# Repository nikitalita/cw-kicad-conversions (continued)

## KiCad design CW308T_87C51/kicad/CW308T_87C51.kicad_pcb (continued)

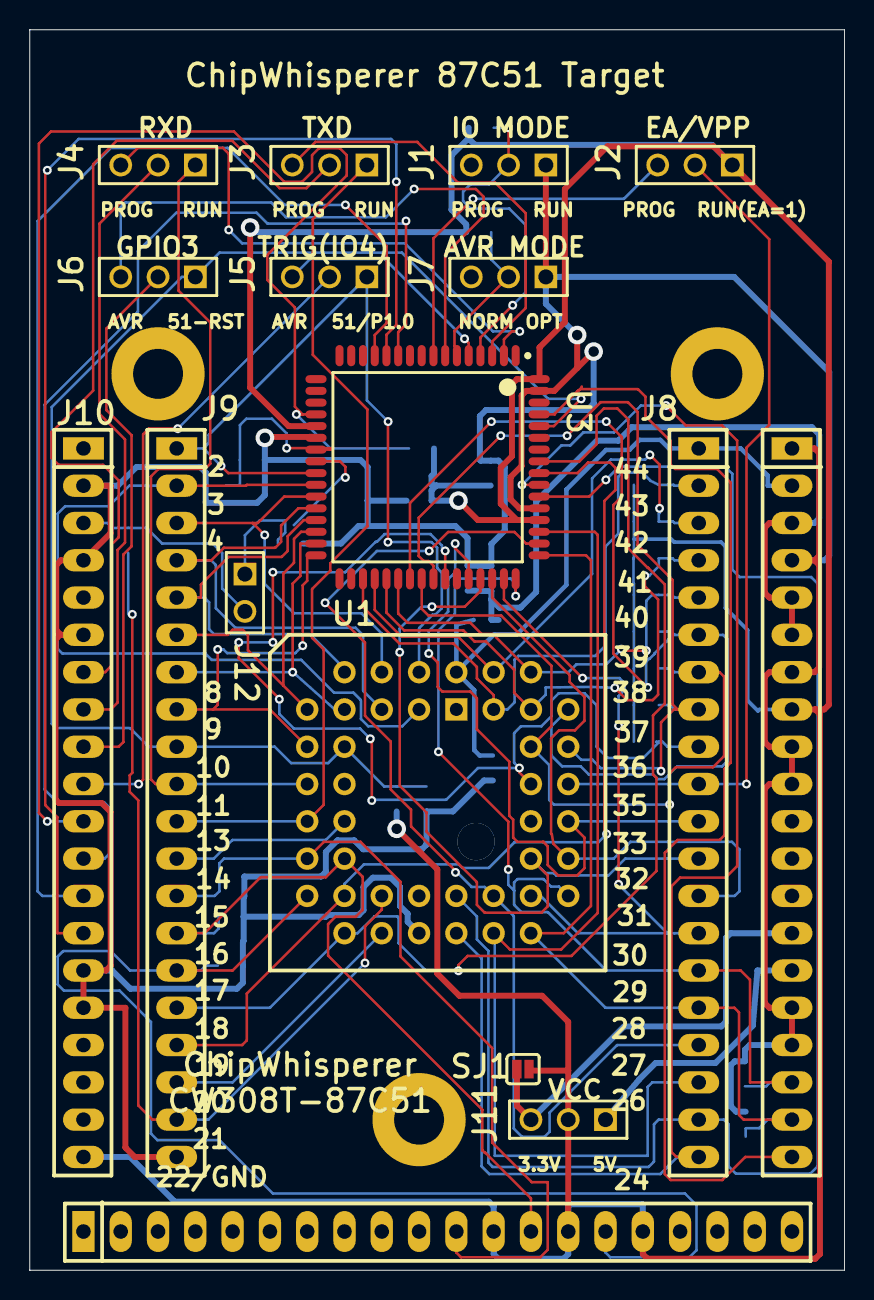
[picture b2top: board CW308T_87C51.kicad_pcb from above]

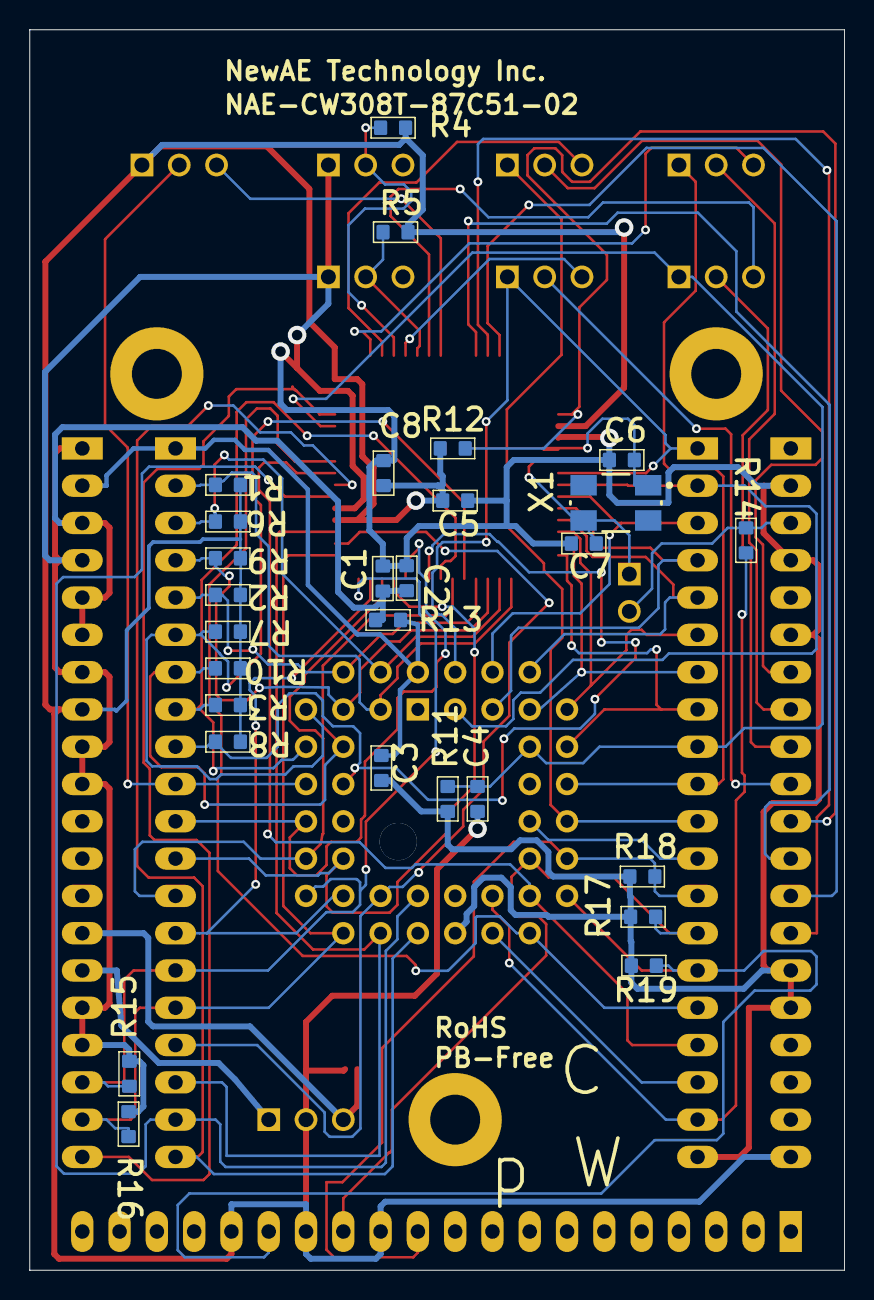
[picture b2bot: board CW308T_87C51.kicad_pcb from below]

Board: 2 copper layers, 55.5 x 84.5 mm, 43 parts (28 on the bottom side), 59 nets.

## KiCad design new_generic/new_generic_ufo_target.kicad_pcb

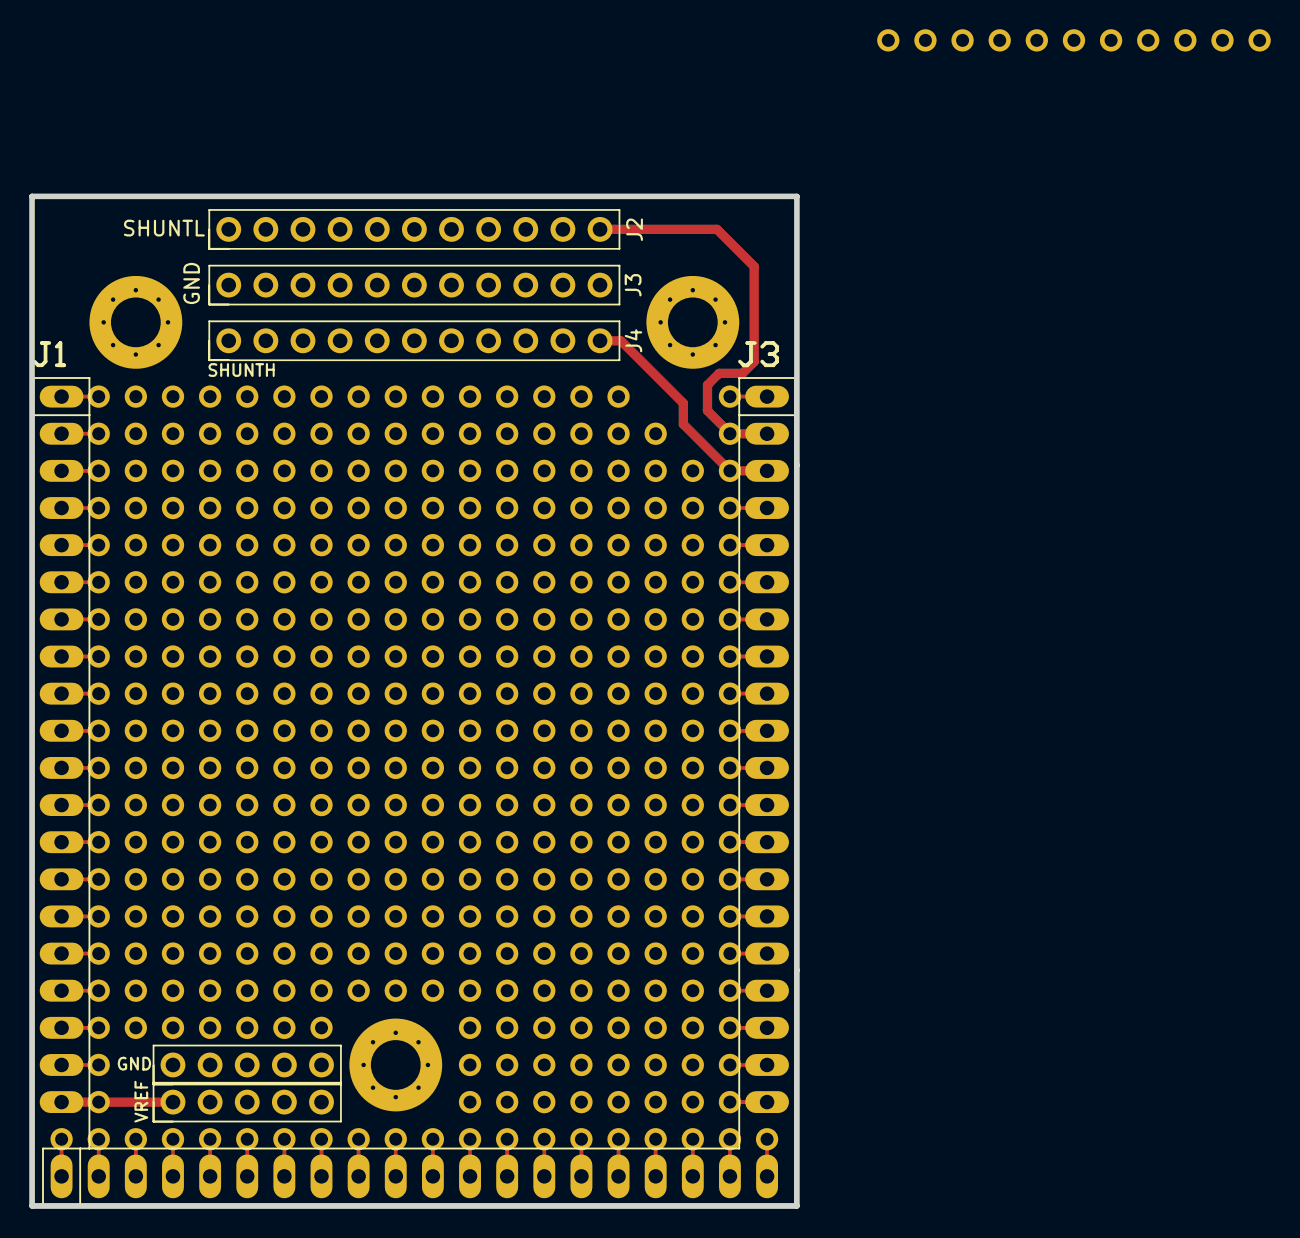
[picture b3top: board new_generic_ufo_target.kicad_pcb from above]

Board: 2 copper layers, 52.3 x 69.1 mm, 6 parts (0 on the bottom side), 4 nets.

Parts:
J1: CW308T_CONNBOARD
J2: SHUNTL; CONNECTED_PinHeader_1x11_P2.54mm_Vertical
J3: GND; CONNECTED_PinHeader_1x11_P2.54mm_Vertical
J4: SHUNTH; CONNECTED_PinHeader_1x11_P2.54mm_Vertical
J5: VREF; CONNECTED_PinHeader_1x05_P2.54mm_Vertical
J6: GND; CONNECTED_PinHeader_1x05_P2.54mm_Vertical

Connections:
GND: J1.A2 (GND), J1.A4 (GND), J1.A6 (GND), J1.A15 (GND), J1.A16 (GND), J1.C1 (GND), J1.C4 (GND), J1.C7 (GND), J1.C9 (GND), J1.C10 (GND), J1.C16 (GND), J1.C17 (GND), J3.1, J6.1
SHUNTH: J1.C3 (SHUNTH), J4.1
VBUS: J1.C2 (SHUNTL), J2.1
VCC: J1.A20 (VREF), J5.1

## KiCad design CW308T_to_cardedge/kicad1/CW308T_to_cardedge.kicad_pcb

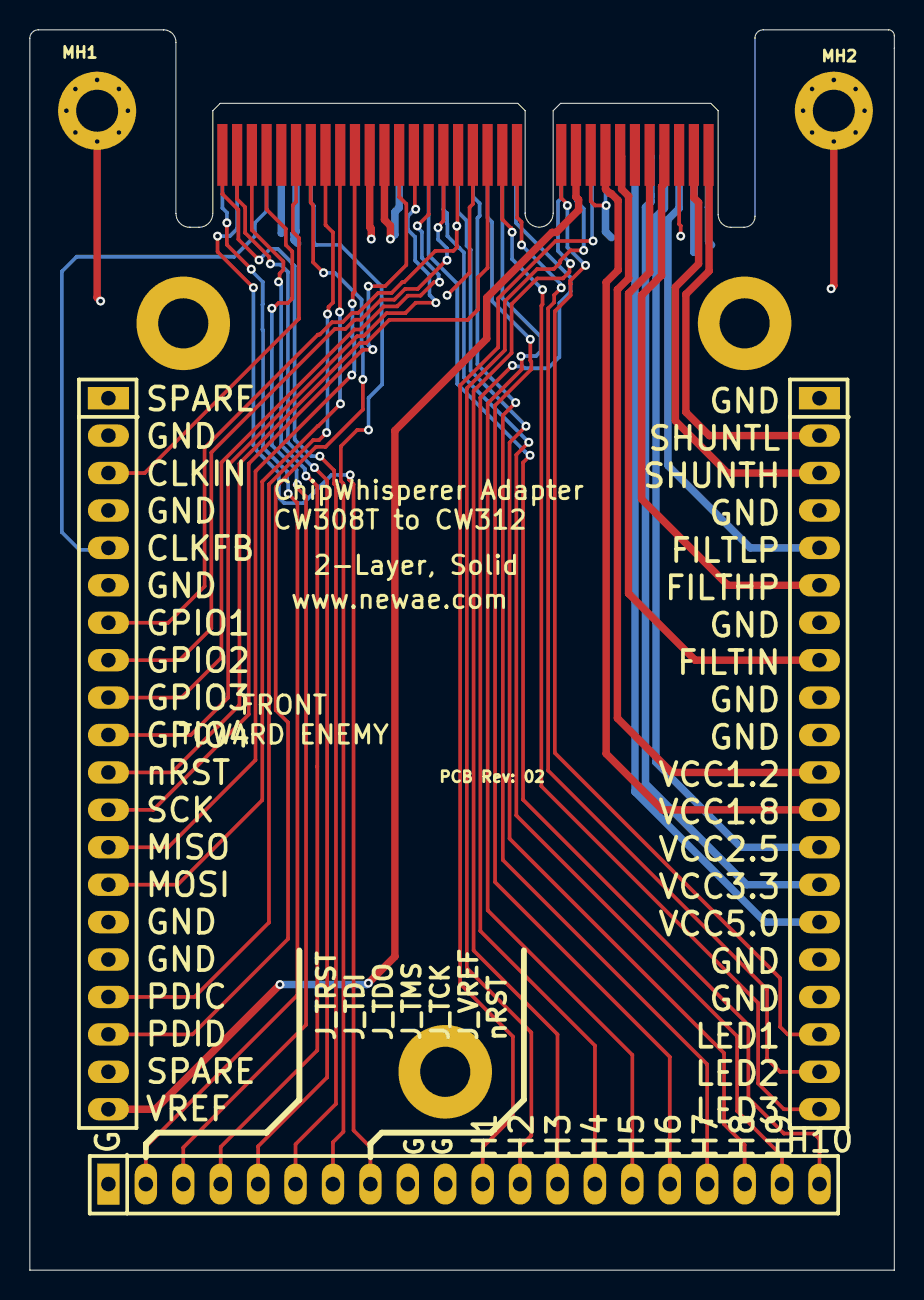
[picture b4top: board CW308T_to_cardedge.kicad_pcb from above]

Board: 2 copper layers, 58.7 x 84.2 mm, 4 parts (0 on the bottom side), 44 nets.

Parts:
J1: CW308_TARGETCON; _Users_cofly_Dropbox (NewAE Technology Inc)_engineering_alt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
MH1, MH2: 4-40 MH, Tight Fit; _Users_colin_Dropbox (NewAE Technology Inc)_engineering_alt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
P1: PCIeX4-GF-2D-1000-1K-O64

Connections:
CLKIN: J1.A5, P1.A29
CLKOUT: J1.A3, P1.B27
FILTIN: J1.C8, P1.B5
FILT_HP: J1.C6, P1.B4
FILT_LP: J1.C5, P1.A3
GND: J1.A2, J1.A4, J1.A6, J1.A15, J1.A16, J1.B1, J1.B9, J1.B10, J1.C1, J1.C4, J1.C7, J1.C9, J1.C10, J1.C16, J1.C17, MH1.1, MH2.1, P1.A1, P1.A2, P1.A8, P1.A20, P1.A27, P1.A28, P1.B3, P1.B9, P1.B15, P1.B21, P1.B22
GPIO1/TX: J1.A7, P1.B16
GPIO2/RX: J1.A8, P1.B17
GPIO3: J1.A9, P1.B18
GPIO4/TRIG: J1.A10, P1.B19
HDR1: J1.B11, P1.A9
HDR2: J1.B12, P1.A10
HDR3: J1.B13, P1.A11
HDR4: J1.B14, P1.A12
HDR5: J1.B15, P1.A13
HDR6: J1.B16, P1.A14
HDR7: J1.B17, P1.A15
HDR8: J1.B18, P1.A16
HDR9: J1.B19, P1.A17
HDR10: J1.B20, P1.A18
IOVREF: J1.A20, P1.B10
JTAG_TCK: J1.B6, P1.B32
JTAG_TDI: J1.B3, P1.B29
JTAG_TDO: J1.B4, P1.B30
JTAG_TMS: J1.B5, P1.B31
JTAG_TRST: J1.B2, P1.A32
JTAG_VREF: J1.B7, P1.A26
JTAG_nRST: J1.B8, P1.A31
LED1: J1.C18, P1.B11
LED2: J1.C19, P1.B12
LED3: J1.C20, P1.B13
MISO: J1.A13, P1.B23
MOSI: J1.A14, P1.B24
PDIC: J1.A17, P1.B25
PDID: J1.A18, P1.B26
SCK: J1.A12, P1.B20
SHUNTH: J1.C3, P1.B2
SHUNTL: J1.C2, P1.B1
VCC1.2: J1.C11, P1.B7
VCC1.8: J1.C12, P1.B8
VCC2.5: J1.C13, P1.A4
VCC3.3: J1.C14, P1.A5
VCC5.0: J1.C15, P1.A6
nRST: J1.A11, P1.B14

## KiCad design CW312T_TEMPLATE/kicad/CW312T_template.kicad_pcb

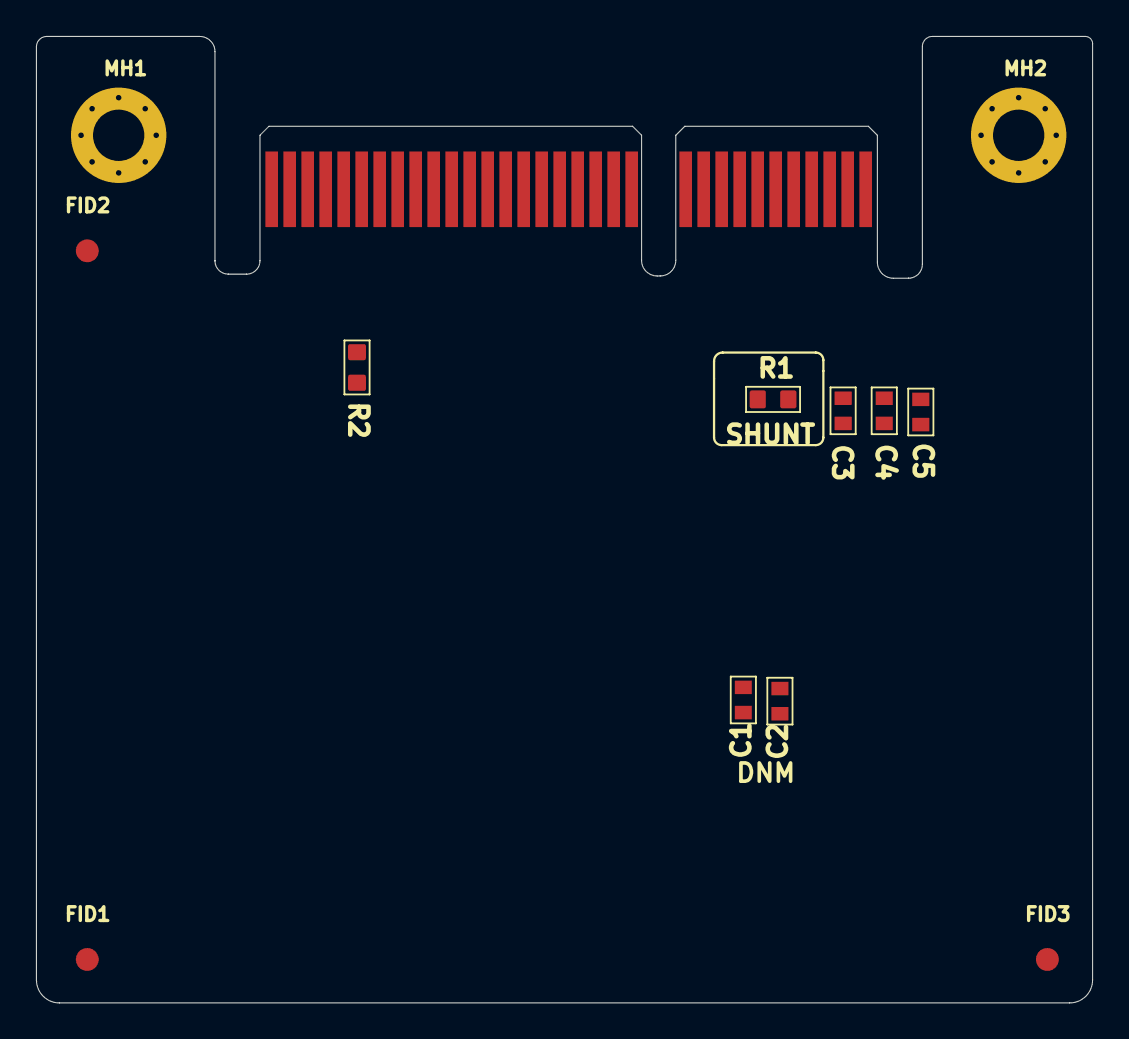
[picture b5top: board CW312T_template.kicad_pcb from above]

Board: 2 copper layers, 58.7 x 53.7 mm, 13 parts (0 on the bottom side), 6 nets, no tracks yet.

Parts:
C1, C2: DNM; CAPC0603_M
C3, C4: 100n; CAPC0603_M
C5: 2u2; CAPC0603_M
FID1, FID2, FID3: FIDU-ROUND-1.0MM; FIDU-ROUND-1.0mm
MH1, MH2: 4-40 MH, Tight Fit; MOUNT_#4_TIGHT
P1: PCIeX4-GF-2D-1000-1K-O64
R1, R2: 10R; RESC1608X55N

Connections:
/CLKIN: P1.B27, R1.1
/FILT_HP: C3.1, C4.1, C5.1, P1.A3, P1.B2, P1.B4, R2.2
/SHUNTL: C1.1, C2.1, P1.B1, R2.1
/nRST: P1.A31, P1.B14
GND: C1.2, C2.2, C3.2, C4.2, C5.2, MH1.1, MH2.1, P1.A1, P1.A2, P1.A8, P1.A20, P1.A27, P1.A28, P1.B3, P1.B9, P1.B15, P1.B21, P1.B22
VCC: P1.A5, P1.A26, P1.B10
